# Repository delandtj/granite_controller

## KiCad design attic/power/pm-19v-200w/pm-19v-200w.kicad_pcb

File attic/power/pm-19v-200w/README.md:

# PM-19V-200W - OBSOLETE

Superseded by PM-19V-250W (power/pm-19v-250w/) on 2026-10-27.
Not for order, no further work. Kept for reference only.

Differences that make it obsolete: DOSA pin mount with a 1x5 1.27 mm
aux header (J2: OV_KILL, PGOOD, ID, TEMP, GND) instead of the screwed
mount and 2x3 aux block of docs/pm-interface.md, and 200 W instead of
250 W. Its silk was never tidied. Any future lower-power module will be
a new design, not a revision of this one.

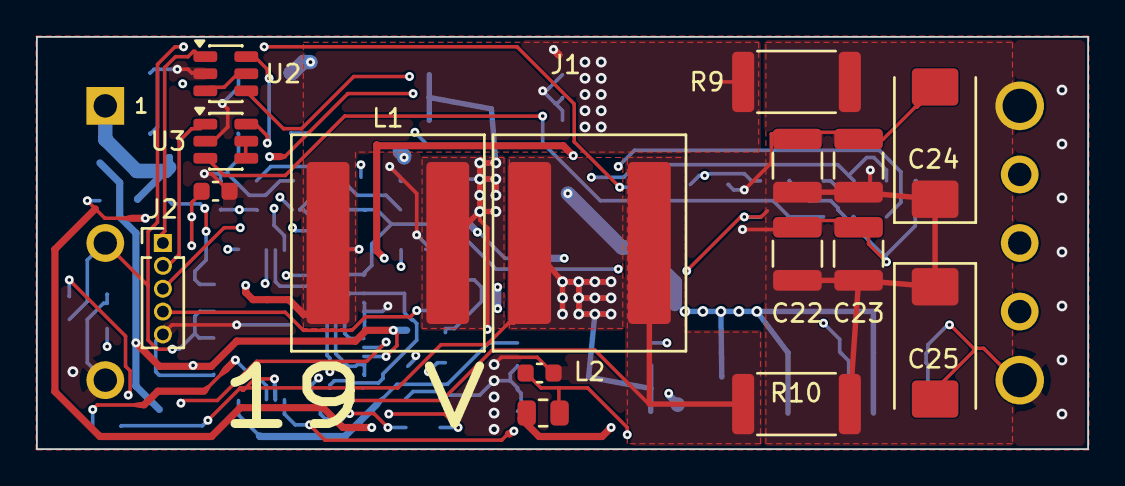
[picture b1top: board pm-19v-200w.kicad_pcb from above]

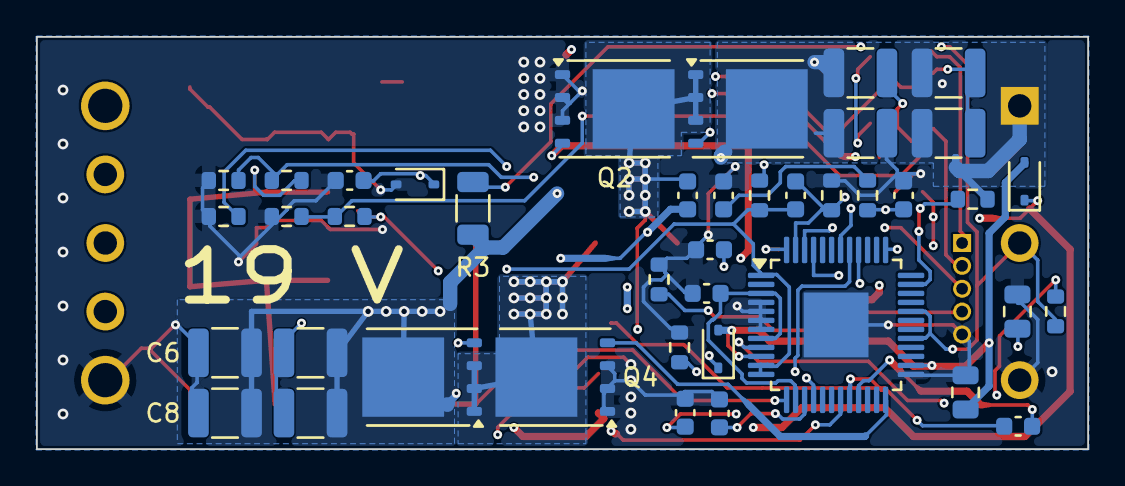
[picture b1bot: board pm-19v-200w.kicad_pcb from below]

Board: 4 copper layers, 58.4 x 22.9 mm, 58 parts (41 on the bottom side), 33 nets.

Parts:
C1, C2, C3, C4, C5, C6, C7, C8: 2.2u; C_1210_3225Metric
C9: 1u 100V; C_0805_2012Metric
C10, C15, C18, C19, C27, C28: 0.1u; C_0603_1608Metric
C11: 4.7u 25V; C_0805_2012Metric
C12: 47p; C_0603_1608Metric
C13: 2.2n; C_0603_1608Metric
C14: 100p; C_0603_1608Metric
C16, C17: 1n; C_0603_1608Metric
C20, C21, C22, C23: 22u; C_1210_3225Metric
C24, C25: 100u; CP_EIA-7343-31_Kemet-D
C26: 1u; C_0603_1608Metric
D1, D2: BAS21; D_SOD-323
D3: 4.7V; D_SOD-323
J1: Brick 1/8 (DOSA); Brick_Eighth_DOSA
J2: Aux; PinHeader_1x05_P1.27mm_Vertical
L1, L2: 22u Isat>=12A; L_Coilcraft_XAL1010-XXX
Q1, Q2, Q3, Q4: BSC070N10NS5; TDSON-8-1
R1: 10R; R_0603_1608Metric
R3: 976k 1206; R_1206_3216Metric
R4: 12.4k; R_0603_1608Metric
R5: 19.6k; R_0603_1608Metric
R6: 180k; R_0603_1608Metric
R7, R13, R15: 10k; R_0603_1608Metric
R8: 15k; R_0603_1608Metric
R9, R10: 8m 2512; R_2512_6332Metric
R11: 47k 0805; R_0805_2012Metric
R12: 178k; R_0603_1608Metric
R14: 133k; R_0603_1608Metric
R16: 10k (ID); R_0603_1608Metric
TH1: 10k NTC; R_0603_1608Metric
U1: LTC7810; LQFP-48-1EP_7x7mm_P0.5mm_EP3.6x3.6mm
U2, U3: MCP65R46-1.21; SOT-23-6

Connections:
/BG1: Q2.4, U1.37
/BG2: Q4.4, U1.24
/BOOST1: C18.1, D1.1, U1.40
/BOOST2: C19.1, D2.1, U1.21
/DRVCC: C11.1, D1.2, D2.2, U1.10, U1.26
/ID: J2.3, R16.1
/INTVCC: C10.1, U1.3, U1.8, U1.14
/OVLO: R4.2, R5.1, U1.9
/OV_KILL: J2.1, U2.1
/OV_REF: U2.3, U2.5
/PGOOD: J2.2, U3.1
/PG_REF: U3.4, U3.5
/RUN: J1.2, R3.2, R4.1, U1.29, U1.32
/SNS1P: L1.2, R9.1, U1.48
/SNS2P: L2.2, R10.1, U1.13
/SW1: C18.2, L1.1, Q1.1, Q1.2, Q1.3, Q2.5, U1.41
/SW2: C19.2, L2.1, Q3.1, Q3.2, Q3.3, Q4.5, U1.20
/TEMP: J2.4, TH1.1
/TG1: Q1.4, U1.42
/TG2: Q3.4, U1.19
/VAUX: C26.1, C27.1, C28.1, D3.1, R11.2, U2.6, U3.6
/VIN: C1.1, C2.1, C3.1, C4.1, C5.1, C6.1, C7.1, C8.1, J1.1, Q1.5, Q3.5, R1.1, R3.1, R11.1
/VIN_IC: C9.1, R1.2, U1.35
/VOUT: C12.1, C20.1, C21.1, C22.1, C23.1, C24.1, C25.1, J1.8, R6.1, R9.2, R10.2, R12.1, R14.1, U1.1, U1.11, U1.12
GND: C1.2, C2.2, C3.2, C4.2, C5.2, C6.2, C7.2, C8.2, C9.2, C10.2, C11.2, C13.2, C14.2, C15.2, C16.2, C17.2, C20.2, C21.2, C22.2, C23.2, C24.2, C25.2, C26.2, C27.2, C28.2, D3.2, J1.3, J1.4, J2.5, Q2.1, Q2.2, Q2.3, Q4.1, Q4.2, Q4.3, R5.2, R7.2, R13.2, R15.2, R16.2, TH1.2, U1.4, U1.5, U1.6, U1.7, U1.25, U1.49, U2.2, U3.2
unnamed: C13.1, R8.2
unnamed: C14.1, R8.1, U1.46
unnamed: C16.1, U1.15
unnamed: C15.1, U1.45
unnamed: C17.1, U1.16
unnamed: C12.2, R6.2, R7.1, U1.47
unnamed: R12.2, R13.1, U2.4
unnamed: R14.2, R15.1, U3.3

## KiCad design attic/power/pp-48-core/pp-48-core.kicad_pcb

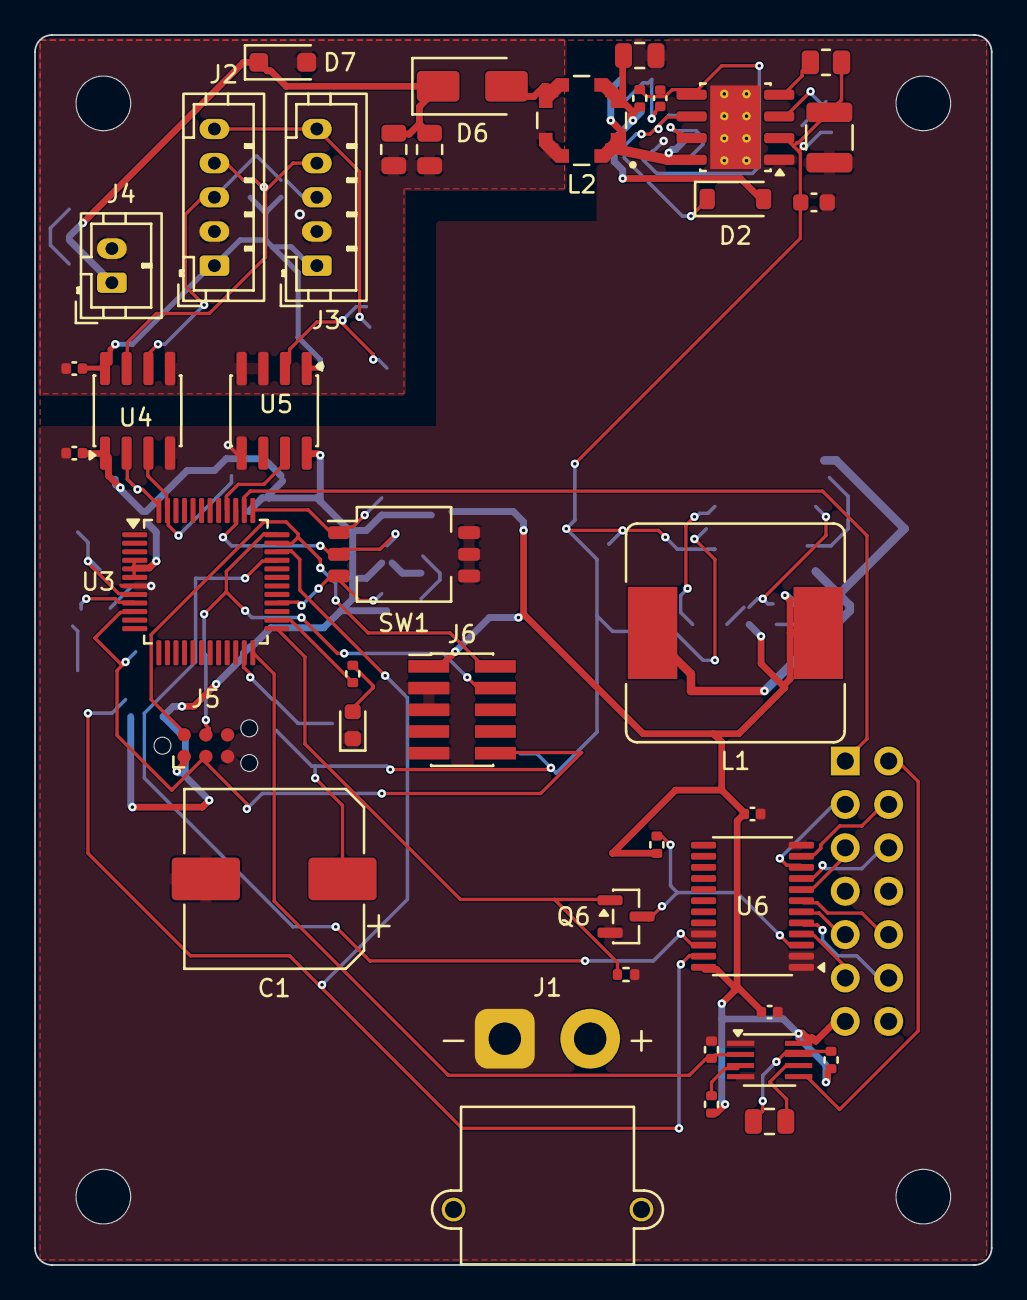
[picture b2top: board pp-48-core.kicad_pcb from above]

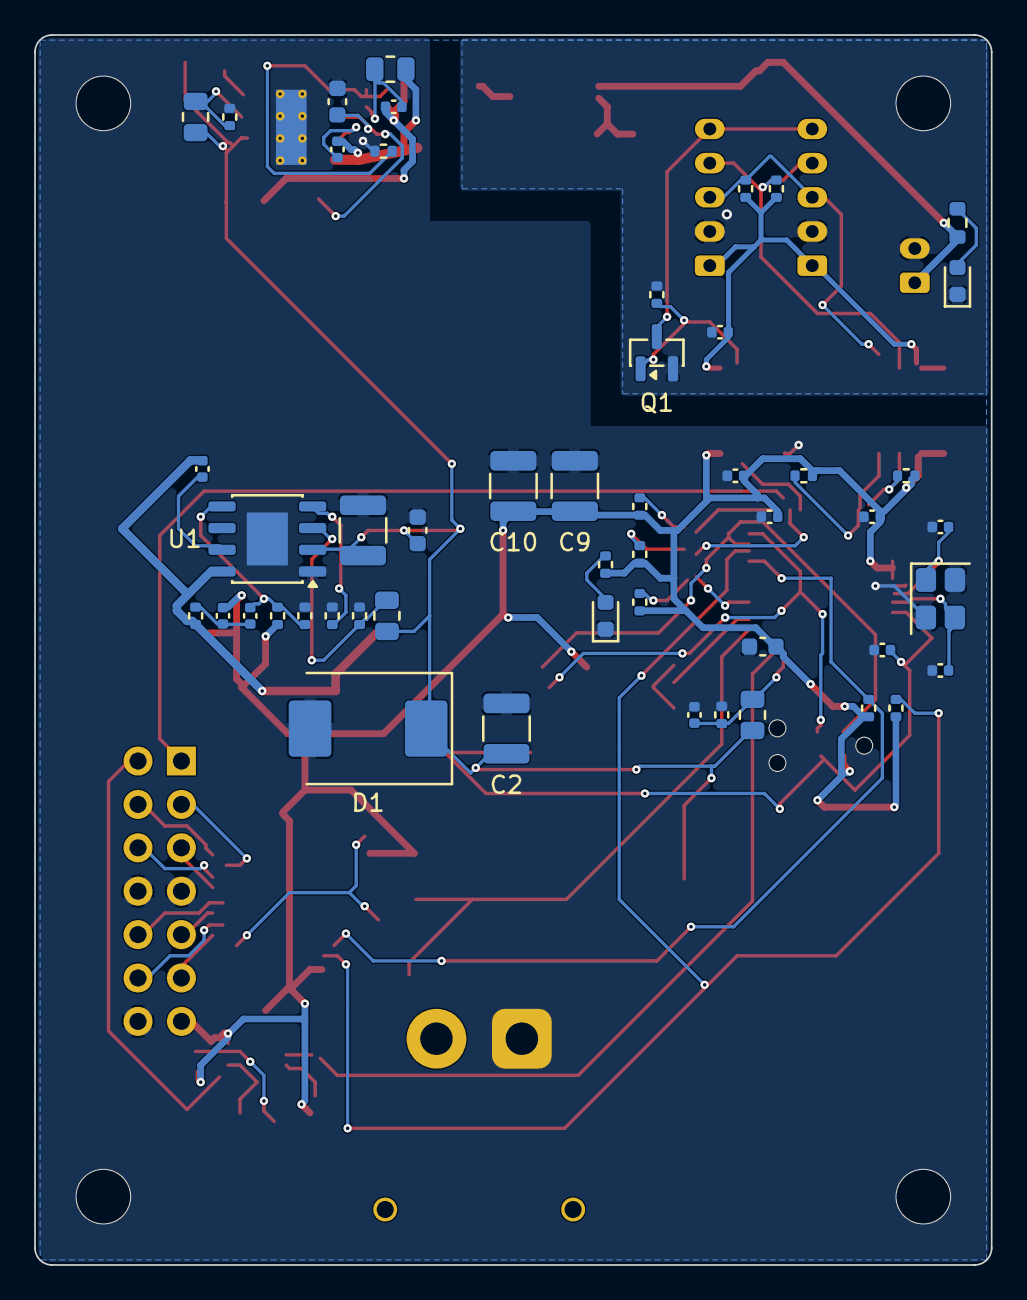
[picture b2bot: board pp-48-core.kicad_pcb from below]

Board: 4 copper layers, 56.0 x 72.0 mm, 95 parts (51 on the bottom side), 59 nets.

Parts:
C1: 47u 100V; CP_Elec_10x10
C2, C7, C11: 2.2u 100V; C_1210_3225Metric
C4: 2.2n 50V; C_0402_1005Metric
C5: 1.5n; C_0402_1005Metric
C6, C15, C17, C18, C20, C21, C24, C25, C26, C27, C28, C302: 100n; C_0402_1005Metric
C8, C12: 100n 100V; C_0603_1608Metric
C9, C10: 22u 10V; C_1210_3225Metric
C13: 10n 50V; C_0402_1005Metric
C14: 1n; C_0402_1005Metric
C16: 1u 25V; C_0603_1608Metric
C19: 4.7u; C_0603_1608Metric
C22, C23: 33p; C_0402_1005Metric
C29: 4.7u 25V; C_0805_2012Metric
C30, C31: 10u 25V; C_0805_2012Metric
C301: 10u; C_0805_2012Metric
D1: SMDJ60A; D_SMC
D2: 1N4148W; D_SOD-123
D3: GREEN 3V3; LED_0603_1608Metric
D4: GREEN RUN; LED_0603_1608Metric
D5: GREEN 12V; LED_0603_1608Metric
D6: SS110; D_SMA
D7: SMF13A; D_SOD-123F
H1, H2, H3, H4: MountingHole_3.2mm_M3
J1: XT30PW-M; AMASS_XT30PW-M_1x02_P2.50mm_Horizontal
J2: CTRL IN; JST_PH_B5B-PH-K_1x05_P2.00mm_Vertical
J3: CTRL OUT; JST_PH_B5B-PH-K_1x05_P2.00mm_Vertical
J4: 12V AUX OUT; JST_PH_B2B-PH-K_1x02_P2.00mm_Vertical
J5: SWD; Tag-Connect_TC2030-IDC-NL_2x03_P1.27mm_Vertical
J6: SWD; PinHeader_2x05_P1.27mm_Vertical_SMD
J301: CHAIN OUT; PinSocket_2x07_P2.54mm_Horizontal
L1: 33u; L_Bourns_SRR1260
L2: 33u; L_Coilcraft_LPD5030V
Q1, Q6: 2N7002; SOT-23
R3: 1M; R_0805_2012Metric
R4: 52.3k; R_0402_1005Metric
R5: 41.2k; R_0402_1005Metric
R6: 86.6k; R_0402_1005Metric
R7: 49.9k; R_0402_1005Metric
R8: 453k; R_0402_1005Metric
R9: 4.7k; R_0603_1608Metric
R10: 100k; R_0805_2012Metric
R11: 4.22k; R_0402_1005Metric
R12: 169k; R_0805_2012Metric
R13: 200k; R_0805_2012Metric
R14: 18.7k; R_0402_1005Metric
R15: 220k; R_0805_2012Metric
R16, R31, R303: 10k; R_0402_1005Metric
R17: 2k; R_0402_1005Metric
R18, R19: 1k; R_0402_1005Metric
R20, R21, R22, R30, R32, R301, R302: 100k; R_0402_1005Metric
R23, R24: 2.2k; R_0402_1005Metric
R26, R27, R28, R29: 4.7k; R_0402_1005Metric
SW1: ADR; SW_DIP_SPSTx03_Slide_KingTek_DSHP03TS_W7.62mm_P1.27mm
U1: LM5164DDA; HSOP-8-1EP_3.9x4.9mm_P1.27mm_EP2.41x3.1mm
U2: LM5018MRX/NOPB; SOIC-8-1EP_3.9x4.9mm_P1.27mm_EP2.95x4.9mm_Mask2.71x3.4mm_Th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
U3: STM32G070CBT6; LQFP-48_7x7mm_P0.5mm
U4: ISO1640BD; SOIC-8_3.9x4.9mm_P1.27mm
U5: ISO7721D; SOIC-8_3.9x4.9mm_P1.27mm
U6: TCA9548APWR; TSSOP-24_4.4x7.8mm_P0.65mm
U301: 74LVC1G123; SSOP-8_2.95x2.8mm_P0.65mm
Y1: 8MHz; Crystal_SMD_3225-4Pin_3.2x2.5mm

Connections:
+3V3: C5.2, C9.1, C10.1, C18.1, C19.1, C20.1, C25.1, C27.1, C28.1, C302.1, J5.1, J6.1, J301.13, L1.2, R6.1, R18.1, R20.1, R21.1, R22.1, R23.1, R24.1, R26.1, R27.1, R31.1, R301.1, R303.1, U3.4, U3.5, U3.6, U4.1, U5.8, U6.24, U301.8
/Chain/CEXT: C301.2, U301.6
/Chain/PRESS_CLRN: R303.2, U301.3
/Chain/PRESS_EN: J301.2, U301.5
/Chain/RCEXT: C301.1, R301.2, U301.7
/EXP_RSTN: J301.1, U3.38
/INT_OUT: U3.40, U5.7
/Link/CTRL_INT: J2.5, J3.5, Q1.3
/Link/CTRL_SCL: J2.3, J3.3, R29.2, U4.6
/Link/CTRL_SDA: J2.4, J3.4, R28.2, U4.7
/Link/ISO_OUTA: Q1.1, R30.1, U5.2
/MCU/ADR0: R20.2, SW1.1, U3.37
/MCU/ADR1: R21.2, SW1.2, U3.39
/MCU/ADR2: R22.2, SW1.3, U3.28
/MCU/LEDRUN_A: D4.2, R19.2
/MCU/LED_RUN: R19.1, U3.26
/MCU/NRST: C21.1, J5.3, J6.10, U3.10
/MCU/OSC_IN: C22.1, U3.8, Y1.1
/MCU/OSC_OUT: C23.1, U3.9, Y1.3
/MCU/SWCLK: J5.4, J6.4, U3.36
/MCU/SWDIO: J5.2, J6.2, U3.35
/MUX_RST: Q6.1, R32.1, U3.25
/Mux/MUX_RSTN: Q6.3, R31.2, U6.3
/PRESS_TRIG: R302.1, U3.24, U301.2
/SCL1: R27.2, U3.47, U4.3
/SCL2: R24.2, U3.33, U6.22
/SDA1: R26.2, U3.48, U4.2
/SDA2: R23.2, U3.34, U6.23
/Supplies/BST1: C4.1, U1.7
/Supplies/BST2: C13.1, U2.7
/Supplies/EN1: R3.2, R4.1, U1.3
/Supplies/FB1: C6.2, R6.2, R7.1, U1.5
/Supplies/FB2: C15.2, R14.2, R17.1, U2.5
/Supplies/INJ1: C5.1, C6.1, R8.2
/Supplies/INJ2: C14.1, C15.1, R13.2
/Supplies/LED12_A: D5.2, R9.2
/Supplies/LED33_A: D3.2, R18.2
/Supplies/RON1: R5.1, U1.4
/Supplies/RON2: R12.2, U2.4
/Supplies/SEC2: D6.2, L2.3
/Supplies/SW1: C4.2, L1.1, R8.1, U1.8
/Supplies/SW2: C13.2, L2.1, R13.1, U2.8
/Supplies/UVLO2: R10.2, R11.1, U2.3
/Supplies/VCC2: C16.1, D2.1, U2.6
/Supplies/VOUT1: C14.2, C29.1, D2.2, L2.2, R14.1
/UNIT1_SCL: J301.12, U6.5
/UNIT1_SDA: J301.11, U6.4
/UNIT2_SCL: J301.10, U6.7
/UNIT2_SDA: J301.9, U6.6
/UNIT3_SCL: J301.6, U6.9
/UNIT3_SDA: J301.5, U6.8
/UNIT4_SCL: J301.4, U6.11
/UNIT4_SDA: J301.3, U6.10
/VIN_SNS: C17.1, R15.2, R16.1, U3.23
CTRL_3V3: C24.1, C26.1, J2.1, J3.1, R28.1, R29.1, U4.8, U5.1
CTRL_12V: C30.1, C31.1, D6.1, D7.1, J4.1, R9.1
CTRL_GND: C24.2, C26.2, C30.2, C31.2, D5.1, D7.2, J2.2, J3.2, J4.2, L2.4, Q1.2, R30.2, U4.5, U5.3, U5.4
GND: C1.2, C2.2, C7.2, C8.2, C9.2, C10.2, C11.2, C12.2, C16.2, C17.2, C18.2, C19.2, C20.2, C21.2, C22.2, C23.2, C25.2, C27.2, C28.2, C29.2, C302.2, D1.2, D3.1, D4.1, J1.1, J5.5, J6.3, J6.5, J6.9, J301.7, J301.8, J301.14, Q6.2, R4.2, R5.2, R7.2, R11.2, R16.2, R17.2, R32.2, R302.2, SW1.4, SW1.5, SW1.6, U1.1, U1.9, U2.1, U2.9, U3.7, U4.4, U5.5, U6.1, U6.2, U6.12, U6.21, U301.1, U301.4, Y1.2, Y1.4
VIN: C1.1, C2.1, C7.1, C8.1, C11.1, C12.1, D1.1, J1.2, R3.1, R10.1, R12.1, R15.1, U1.2, U2.2

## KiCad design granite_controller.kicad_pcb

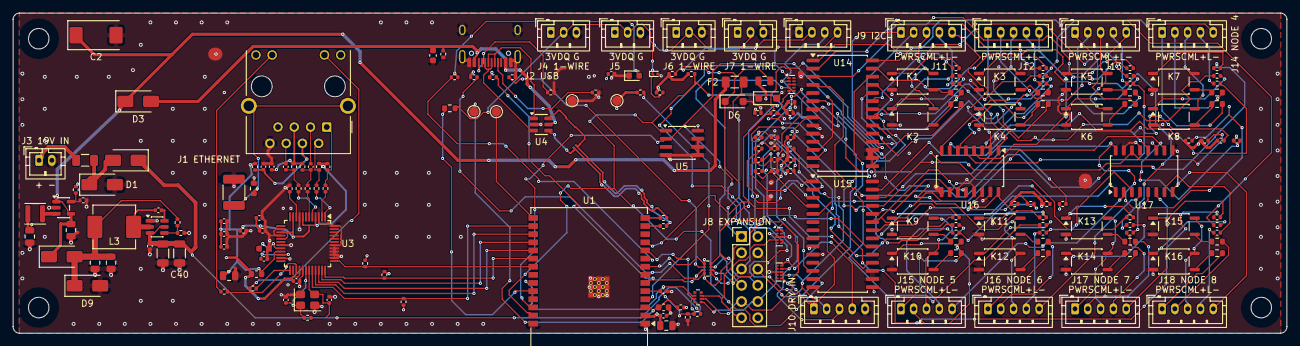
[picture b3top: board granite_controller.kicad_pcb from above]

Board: 4 copper layers, 199.0 x 50.0 mm, 207 parts (0 on the bottom side), 187 nets.

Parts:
C2: 220u/10V Ta-poly; CP_EIA-7343-31_Kemet-D
C3, C4, C44, C45: 22u; C_0805_2012Metric
C5, C6, C7, C8, C9, C10, C11, C13, C15, C38, C46, C47, C48, C49, C50, C51: 100n; C_0402_1005Metric
C12, C32: 10u; C_0805_2012Metric
C14: 1u; C_0603_1608Metric
C26, C27: 15p; C_0402_1005Metric
C28, C29: 6.8n; C_0402_1005Metric
C30: 4.7u; C_0603_1608Metric
C31, C35: 10n; C_0402_1005Metric
C34: 22n; C_0402_1005Metric
C36: 1n/2kV; C_1812_4532Metric
C40, C41: 4.7u/50V; C_1206_3216Metric
C42, C43: 100n/50V; C_0402_1005Metric
C52: 2.2u/25V; C_0603_1608Metric
D1: SMAJ22A; D_SMA
D2, D3, D8: SS34; D_SMA
D4: green; LED_0603_1608Metric
D5: ESD9L5.0ST5G; D_SOD-923
D6: SMF3.3A; D_SOD-123F
D7: SMF5.0A; D_SOD-123F
D9: SMAJ6.0A; D_SMA
F1: PTC 350mA; Fuse_0805_2012Metric
F2: PTC 500mA; Fuse_1206_3216Metric
F3: PTC 0.75A; Fuse_1206_3216Metric
H1, H2, H3, H4: MountingHole_3.2mm_M3
J1: HR911105A; RJ45_Hanrun_HR911105A_Horizontal
J2: TYPE-C-31-M-12; USB_C_Receptacle_HRO_TYPE-C-31-M-12
J3: 19V_IN; JST_PH_B2B-PH-K_1x02_P2.00mm_Vertical
J4, J5, J6, J7: 1WIRE; JST_PH_B3B-PH-K_1x03_P2.00mm_Vertical
J8: EXPANSION; PinHeader_2x06_P2.54mm_Vertical
J9: I2C_SENSOR; JST_PH_B4B-PH-K_1x04_P2.00mm_Vertical
J10: DRY_IN; JST_PH_B5B-PH-K_1x05_P2.00mm_Vertical
J11: MB01_FP; JST_PH_B5B-PH-K_1x05_P2.00mm_Vertical
J12: MB02_FP; JST_PH_B5B-PH-K_1x05_P2.00mm_Vertical
J13: MB03_FP; JST_PH_B5B-PH-K_1x05_P2.00mm_Vertical
J14: MB04_FP; JST_PH_B5B-PH-K_1x05_P2.00mm_Vertical
J15: MB05_FP; JST_PH_B5B-PH-K_1x05_P2.00mm_Vertical
J16: MB06_FP; JST_PH_B5B-PH-K_1x05_P2.00mm_Vertical
J17: MB07_FP; JST_PH_B5B-PH-K_1x05_P2.00mm_Vertical
J18: MB08_FP; JST_PH_B5B-PH-K_1x05_P2.00mm_Vertical
K1, K2, K3, K4, K5, K6, K7, K8, K9, K10, K11, K12, K13, K14, K15, K16: TLP176AM; SOIC-4_4.55x3.7mm_P2.54mm
L1: 2u2 SWPA3015S2R2MT; L_Sunlord_SWPA3015S
L2: 120R@100MHz; L_0603_1608Metric
L3: 3u3; L_Changjiang_FXL0630
R1, R37, R63: 100k; R_0402_1005Metric
R2: 22.1k; R_0402_1005Metric
R3, R4: 330; R_0402_1005Metric
R5, R6, R13, R14, R30, R65: 4.7k; R_0402_1005Metric
R7, R16, R17, R18, R19, R27, R32, R33, R59, R60, R61, R62, R64: 10k; R_0402_1005Metric
R8, R55, R56, R57, R58: 1k; R_0402_1005Metric
R9, R10, R11, R12: 33; R_0402_1005Metric
R15, R38: 12.4k 1%; R_0402_1005Metric
R20, R21, R22, R23: 49.9; R_0402_1005Metric
R24, R25: 5.1k; R_0402_1005Metric
R26: 10; R_0402_1005Metric
R28: 1M; R_0603_1608Metric
R29: 1M; R_0402_1005Metric
R34, R35: 22; R_0402_1005Metric
R36, R201, R202, R203, R204, R205, R206, R207, R208, R209, R210, R211, R212, R213, R214, R215, R216: 100; R_0603_1608Metric
R39, R40, R41, R42, R43, R44, R45, R46: 47k; R_0402_1005Metric
R47, R48, R49, R50, R51, R52, R53, R54: 220; R_0402_1005Metric
R101, R102, R103, R104, R105, R106, R107, R108, R109, R110, R111, R112, R113, R114, R115, R116: 270; R_0402_1005Metric
RN1, RN2: 4x330; R_Array_Convex_4x0402
TP1: EN; TestPoint_Pad_D1.5mm
TP2: BOOT; TestPoint_Pad_D1.5mm
TP3: GND; TestPoint_Pad_D1.5mm
TP4: 3V3; TestPoint_Pad_D1.5mm
U1: ESP32-C6-WROOM-1-N8; ESP32-C6-WROOM-1
U2: TLV62569DBV; SOT-23-5
U3: W5500; LQFP-48_7x7mm_P0.5mm
U4: USBLC6-2SC6; SOT-23-6
U5: TMP1075D; SOIC-8_3.9x4.9mm_P1.27mm
U6, U7, U18: TPD4E05U06DQA; USON-10_2.5x1.0mm_P0.5mm
U8: LMR51430YDDCR; SOT-23-6
U14, U15: MCP23017-E/SO; SOIC-28W_7.5x17.9mm_P1.27mm
U16, U17: TLP290-4; SOP-16_4.55x10.3mm_P1.27mm
Y2: 25MHz 12pF YXC; Crystal_SMD_Abracon_ABM8G-4Pin_3.2x2.5mm

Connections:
+3V3: C4.1, C11.1, C12.1, C13.1, C15.1, C38.1, C46.1, F1.1, J1.9, J1.12, J4.1, J5.1, J6.1, J7.1, L1.1, L2.1, R1.2, R5.1, R6.1, R7.1, R13.1, R14.1, R16.1, R17.1, R18.1, R27.1, R30.1, R33.1, R39.1, R40.1, R41.1, R42.1, R43.1, R44.1, R45.1, R46.1, R59.1, R60.1, R61.1, R62.1, TP4.1, U1.2, U3.28, U5.8, U14.9, U15.9, U15.15
+5V: C2.1, C3.1, D2.1, D3.1, F2.1, U2.1, U2.4
/Ethernet/+3V3A: C5.1, C6.1, C7.1, C8.1, C9.1, C10.1, C32.1, L2.2, R20.2, R21.2, R26.2, U3.4, U3.8, U3.11, U3.15, U3.17, U3.21
/Ethernet/ETH_1V2O: C31.1, U3.22
/Ethernet/ETH_EXRES: R15.1, U3.10
/Ethernet/ETH_LEDK_ACT: J1.11, R4.1
/Ethernet/ETH_LEDK_LINK: J1.10, R3.1
/Ethernet/ETH_LED_ACT: R4.2, U3.27
/Ethernet/ETH_LED_LINK: R3.2, U3.25
/Ethernet/ETH_RCT: C35.1, J1.5, R22.2, R23.2
/Ethernet/ETH_RX+: C28.2, J1.3
/Ethernet/ETH_RX-: C29.2, J1.6
/Ethernet/ETH_RXN: R12.1, U3.5
/Ethernet/ETH_RXN_T: C29.1, R12.2, R23.1
/Ethernet/ETH_RXP: R11.1, U3.6
/Ethernet/ETH_RXP_T: C28.1, R11.2, R22.1
/Ethernet/ETH_SHLD: C36.1, J1.SH, R28.1
/Ethernet/ETH_TCT: C34.1, J1.4, R26.1
/Ethernet/ETH_TOCAP: C30.1, U3.20
/Ethernet/ETH_TX+: J1.1, R9.2, R20.1
/Ethernet/ETH_TX-: J1.2, R10.2, R21.1
/Ethernet/ETH_TXN: R10.1, U3.1
/Ethernet/ETH_TXP: R9.1, U3.2
/Ethernet/ETH_XI: C26.1, R29.1, U3.30, Y2.1
/Ethernet/ETH_XO: C27.1, R29.2, U3.31, Y2.3
/Expansion header/DRYC1: J10.1, R55.2, R59.2, U18.1
/Expansion header/DRYC2: J10.2, R56.2, R60.2, U18.2
/Expansion header/DRYC3: J10.3, R57.2, R61.2, U18.4
/Expansion header/DRYC4: J10.4, R58.2, R62.2, U18.5
/Expansion header/HDR_3V3: D6.1, F1.2, J8.1, J9.2
/Expansion header/HDR_5V: D7.1, F2.2, J8.2
/Expansion header/HDR_INT: J8.8, RN1.4, U6.5
/Expansion header/HDR_IO5: J8.9, RN2.1, U7.1
/Expansion header/HDR_IO8: J8.10, RN2.2, U7.2
/Expansion header/HDR_IO15: J8.11, RN2.3, U7.4
/Expansion header/HDR_SCL: J8.5, J9.4, RN1.1, U6.1
/Expansion header/HDR_SDA: J8.6, J9.3, RN1.2, U6.2
/Expansion header/HDR_nRESET: J8.7, RN1.3, U6.4
/MCU/C6_BOOT: TP2.1, U1.15
/MCU/C6_EN: C14.1, R7.2, TP1.1, U1.3
/MCU/C6_USB_D+: R34.2, U1.14
/MCU/C6_USB_D-: R35.2, U1.13
/MCU/LED_A: D4.2, R8.2
/MCU/LED_HB: R8.1, U1.9
/MCU/OW_DATA: D5.1, J4.2, J5.2, J6.2, J7.2, R30.2, R36.2
/MCU/OW_MCU: R36.1, U1.24, U1.25
/MCU/USB_CC1: J2.A5, R25.1
/MCU/USB_CC2: J2.B5, R24.1
/MCU/USB_CONN_D+: J2.A6, J2.B6, U4.3
/MCU/USB_CONN_D-: J2.A7, J2.B7, U4.1
/MCU/USB_D+: R34.1, U4.4
/MCU/USB_D-: R35.1, U4.6
/Power/BUCK_5V: C44.1, C45.1, D2.2, D9.1, L3.2, R37.1
/Power/FB_3V3: R1.1, R2.1, U2.5
/Power/FB_5V: R37.2, R38.1, U8.4
/Power/SW_3V3: L1.2, U2.3
/Power/SW_5V: C43.2, L3.1, U8.2
/Power/VIN_19V: C40.1, C41.1, C42.1, D8.1, R63.1, U8.3, U8.5
/Power/VIN_RAW: F3.1, J3.1
/Relay channels/MB1_COM: J11.3, K1.6, K2.6
/Relay channels/MB1_PLED_N: J11.5, U16.2
/Relay channels/MB1_PLED_P: J11.4, R47.1
/Relay channels/MB1_PWR_B: J11.1, R202.2
/Relay channels/MB1_RST_B: J11.2, R201.2
/Relay channels/MB2_COM: J12.3, K3.6, K4.6
/Relay channels/MB2_PLED_N: J12.5, U16.4
/Relay channels/MB2_PLED_P: J12.4, R48.1
/Relay channels/MB2_PWR_B: J12.1, R204.2
/Relay channels/MB2_RST_B: J12.2, R203.2
/Relay channels/MB3_COM: J13.3, K5.6, K6.6
/Relay channels/MB3_PLED_N: J13.5, U16.6
/Relay channels/MB3_PLED_P: J13.4, R49.1
/Relay channels/MB3_PWR_B: J13.1, R206.2
/Relay channels/MB3_RST_B: J13.2, R205.2
/Relay channels/MB4_COM: J14.3, K7.6, K8.6
/Relay channels/MB4_PLED_N: J14.5, U16.8
/Relay channels/MB4_PLED_P: J14.4, R50.1
/Relay channels/MB4_PWR_B: J14.1, R208.2
/Relay channels/MB4_RST_B: J14.2, R207.2
/Relay channels/MB5_COM: J15.3, K9.6, K10.6
/Relay channels/MB5_PLED_N: J15.5, U17.2
/Relay channels/MB5_PLED_P: J15.4, R51.1
/Relay channels/MB5_PWR_B: J15.1, R210.2
/Relay channels/MB5_RST_B: J15.2, R209.2
/Relay channels/MB6_COM: J16.3, K11.6, K12.6
/Relay channels/MB6_PLED_N: J16.5, U17.4
/Relay channels/MB6_PLED_P: J16.4, R52.1
/Relay channels/MB6_PWR_B: J16.1, R212.2
/Relay channels/MB6_RST_B: J16.2, R211.2
/Relay channels/MB7_COM: J17.3, K13.6, K14.6
/Relay channels/MB7_PLED_N: J17.5, U17.6
/Relay channels/MB7_PLED_P: J17.4, R53.1
/Relay channels/MB7_PWR_B: J17.1, R214.2
/Relay channels/MB7_RST_B: J17.2, R213.2
/Relay channels/MB8_COM: J18.3, K15.6, K16.6
/Relay channels/MB8_PLED_N: J18.5, U17.8
/Relay channels/MB8_PLED_P: J18.4, R54.1
/Relay channels/MB8_PWR_B: J18.1, R216.2
/Relay channels/MB8_RST_B: J18.2, R215.2
/Relay channels/NODE_ON1: R39.2, U15.21, U16.16
/Relay channels/NODE_ON2: R40.2, U15.22, U16.14
/Relay channels/NODE_ON3: R41.2, U15.23, U16.12
/Relay channels/NODE_ON4: R42.2, U15.24, U16.10
/Relay channels/NODE_ON5: R43.2, U15.25, U17.16
/Relay channels/NODE_ON6: R44.2, U15.26, U17.14
/Relay channels/NODE_ON7: R45.2, U15.27, U17.12
/Relay channels/NODE_ON8: R46.2, U15.5, U17.10
/Relay channels/PWR_DRV1: R102.1, U14.21
/Relay channels/PWR_DRV2: R104.1, U14.22
/Relay channels/PWR_DRV3: R106.1, U14.23
/Relay channels/PWR_DRV4: R108.1, U14.24
/Relay channels/PWR_DRV5: R110.1, U14.25
/Relay channels/PWR_DRV6: R112.1, U14.26
/Relay channels/PWR_DRV7: R114.1, U14.27
/Relay channels/PWR_DRV8: R116.1, U14.28
/Relay channels/RST_DRV1: R101.1, U14.1
/Relay channels/RST_DRV2: R103.1, U14.2
/Relay channels/RST_DRV3: R105.1, U14.3
/Relay channels/RST_DRV4: R107.1, U14.4
/Relay channels/RST_DRV5: R109.1, U14.5
/Relay channels/RST_DRV6: R111.1, U14.6
/Relay channels/RST_DRV7: R113.1, U14.7
/Relay channels/RST_DRV8: R115.1, U14.8
DRY_IN1: C47.1, R55.1, U15.1
DRY_IN2: C48.1, R56.1, U15.2
DRY_IN3: C49.1, R57.1, U15.3
DRY_IN4: C50.1, R58.1, U15.4
ETH_CS: R16.2, U1.16, U3.32
ETH_INT: R17.2, U1.20, U3.36
ETH_MISO: U1.19, U3.34
ETH_MOSI: U1.18, U3.35
ETH_RST: R18.2, U1.21, U3.37
ETH_SCLK: U1.17, U3.33
EXP_INT: R33.2, RN1.5, U1.8, U14.20, U15.20
EXP_nRESET: R19.1, RN1.6, U1.4
EXP_nRESET_INT: R32.1, U1.11, U14.18, U15.18
GND: C2.2, C3.2, C4.2, C5.2, C6.2, C7.2, C8.2, C9.2, C10.2, C11.2, C12.2, C13.2, C14.2, C15.2, C26.2, C27.2, C30.2, C31.2, C32.2, C34.2, C35.2, C36.2, C38.2, C40.2, C41.2, C42.2, C44.2, C45.2, C46.2, C47.2, C48.2, C49.2, C50.2, C51.2, C52.2, D1.2, D4.1, D5.2, D6.2, D7.2, D9.2, J1.8, J2.A1, J2.A12, J2.B1, J2.B12, J2.SH, J3.2, J4.3, J5.3, J6.3, J7.3, J8.3, J8.4, J8.12, J9.1, J10.5, K1.3, K2.3, K3.3, K4.3, K5.3, K6.3, K7.3, K8.3, K9.3, K10.3, K11.3, K12.3, K13.3, K14.3, K15.3, K16.3, R2.2, R15.2, R19.2, R24.2, R25.2, R28.2, R32.2, R38.2, R64.2, R65.2, TP3.1, U1.1, U1.28, U1.29, U2.2, U3.3, U3.9, U3.14, U3.16, U3.19, U3.23, U3.29, U3.38, U3.39, U3.40, U3.41, U3.42, U3.48, U4.2, U5.4, U5.5, U5.6, U5.7, U6.3, U6.8, U7.3, U7.8, U8.1, U14.10, U14.15, U14.16, U14.17, U15.10, U15.16, U15.17, U16.9, U16.11, U16.13, U16.15, U17.9, U17.11, U17.13, U17.15, U18.3, U18.8, Y2.2, Y2.4
GPIO_IO8: R27.2, RN2.7, U1.10
GPIO_IO15: RN2.6, U1.23
I2C_EXT_SCL: R13.2, RN1.8, U1.7
I2C_EXT_SDA: R14.2, RN1.7, U1.6
I2C_INT_SCL: R5.2, U1.26, U5.2, U14.12, U15.12
I2C_INT_SDA: R6.2, U1.27, U5.1, U14.13, U15.13
unnamed: D1.1, D8.2, F3.2
unnamed: K1.1, R101.2
unnamed: K1.4, R201.1
unnamed: K2.1, R102.2
unnamed: K2.4, R202.1
unnamed: K3.1, R103.2
unnamed: K3.4, R203.1
unnamed: K4.1, R104.2
unnamed: K4.4, R204.1
unnamed: K5.1, R105.2
unnamed: K5.4, R205.1
unnamed: K6.1, R106.2
unnamed: K6.4, R206.1
unnamed: K7.1, R107.2
unnamed: K7.4, R207.1
unnamed: K8.1, R108.2
unnamed: K8.4, R208.1
unnamed: K9.1, R109.2
unnamed: K9.4, R209.1
unnamed: K10.1, R110.2
unnamed: K10.4, R210.1
unnamed: K11.1, R111.2
unnamed: K11.4, R211.1
unnamed: K12.1, R112.2
unnamed: K12.4, R212.1
unnamed: K13.1, R113.2
unnamed: K13.4, R213.1
unnamed: K14.1, R114.2
unnamed: K14.4, R214.1
unnamed: K15.1, R115.2
unnamed: K15.4, R215.1
unnamed: K16.1, R116.2
unnamed: K16.4, R216.1
unnamed: R47.2, U16.1
unnamed: R48.2, U16.3
unnamed: R49.2, U16.5
unnamed: R50.2, U16.7
unnamed: R51.2, U17.1
unnamed: R52.2, U17.3
unnamed: R53.2, U17.5
unnamed: R54.2, U17.7
unnamed: C43.1, U8.6
VBUS: C52.1, D3.2, J2.A4, J2.A9, J2.B4, J2.B9, R65.1, U4.5
VIN_SENSE: C51.1, R63.2, R64.1, U1.5

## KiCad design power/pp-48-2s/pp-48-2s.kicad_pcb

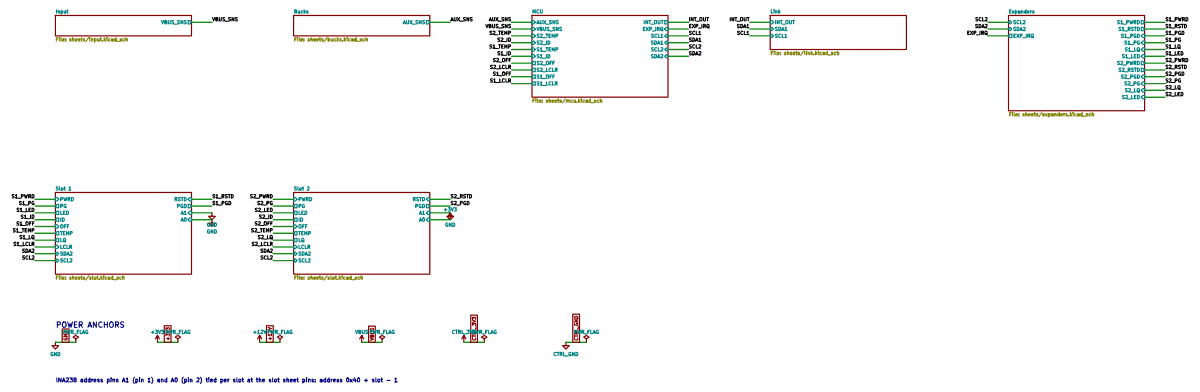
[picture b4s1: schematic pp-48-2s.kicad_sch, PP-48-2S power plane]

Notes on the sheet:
POWER ANCHORS
INA238 address pins A1 (pin 1) and A0 (pin 2) tied per slot at the slot sheet pins: address 0x40 + slot - 1

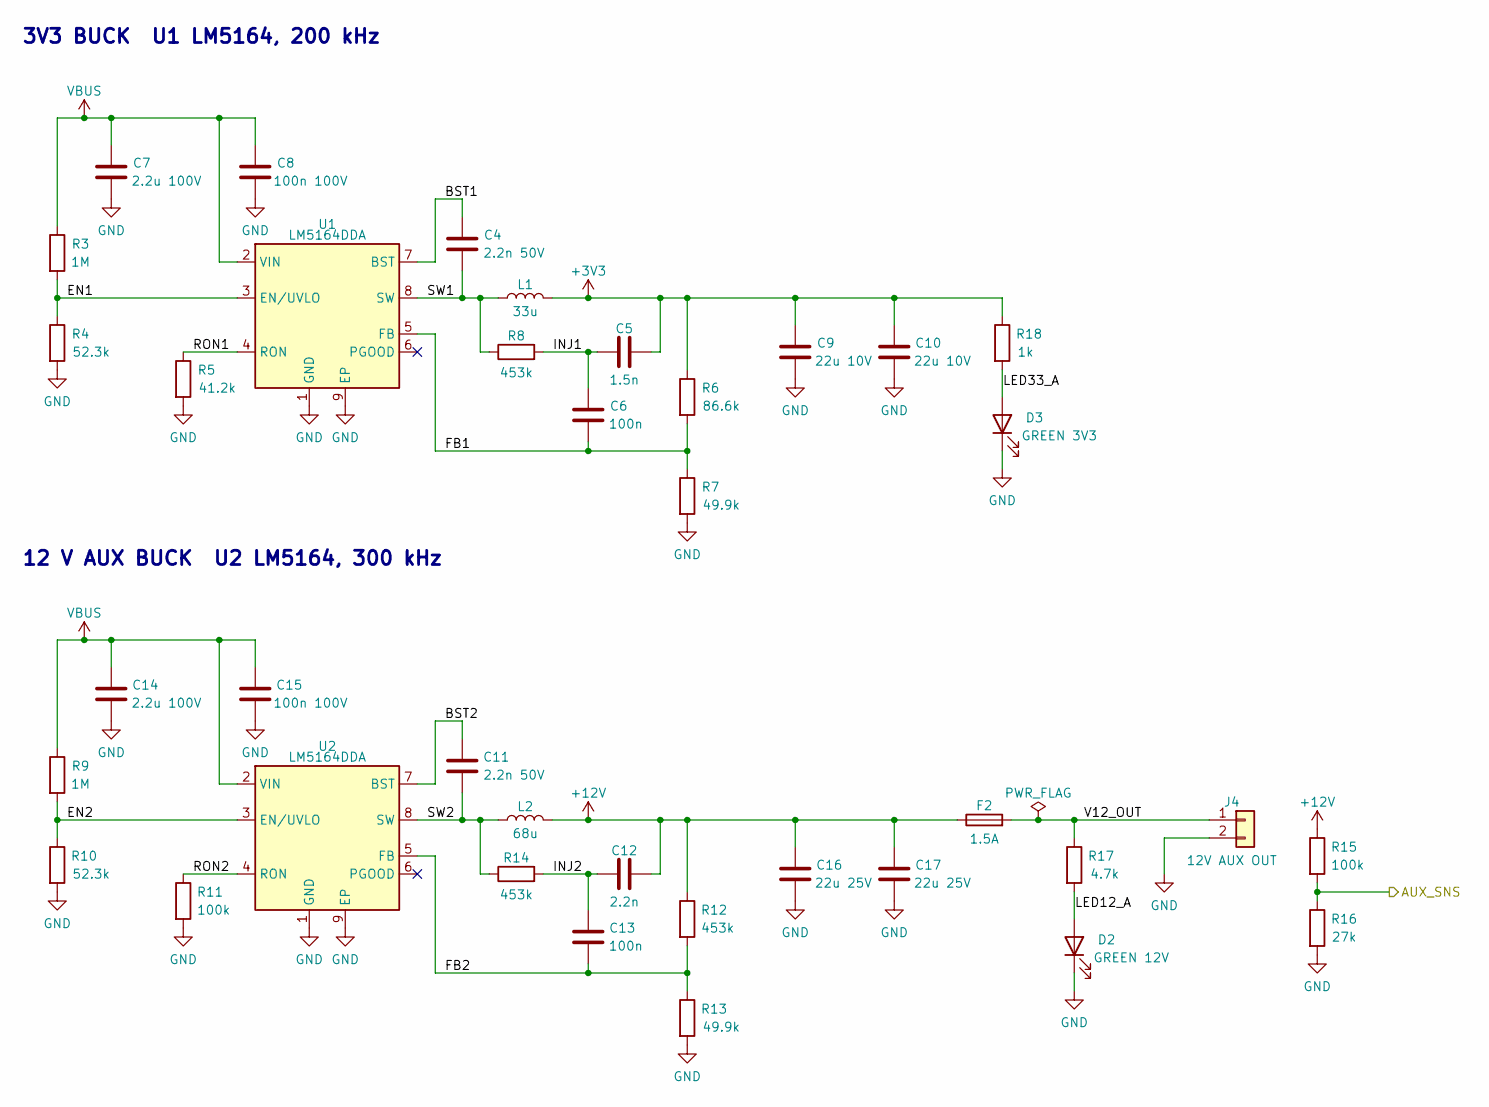
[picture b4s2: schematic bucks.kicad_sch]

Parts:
C4, C11: 2.2n 50V; C_0402_1005Metric
C5: 1.5n; C_0402_1005Metric
C6, C13: 100n; C_0402_1005Metric; LCSC C1525
C7, C14: 2.2u 100V; C_1210_3225Metric; LCSC C338133
C8, C15: 100n 100V; C_0603_1608Metric
C9, C10: 22u 10V; C_1210_3225Metric
C12: 2.2n; C_0402_1005Metric
C16, C17: 22u 25V; C_1210_3225Metric
D2: GREEN 12V; LED_0603_1608Metric; LCSC C2297
D3: GREEN 3V3; LED_0603_1608Metric; LCSC C2297
F2: 1.5A; Fuse_1206_3216Metric
J4: 12V AUX OUT; JST_PH_B2B-PH-K_1x02_P2.00mm_Vertical; LCSC C131337
L1: 33u; L_12x12mm_H6mm; MPN Bourns SRR1260-330M; LCSC C840528
L2: 68u; L_12x12mm_H6mm; MPN Bourns SRR1260-680M
R3, R9: 1M; R_0805_2012Metric
R4, R10: 52.3k; R_0402_1005Metric
R5: 41.2k; R_0402_1005Metric
R6: 86.6k; R_0402_1005Metric
R7, R13: 49.9k; R_0402_1005Metric
R8, R12, R14: 453k; R_0402_1005Metric
R11, R15: 100k; R_0402_1005Metric; LCSC C25741
R16: 27k; R_0402_1005Metric
R17: 4.7k; R_0603_1608Metric
R18: 1k; R_0402_1005Metric; LCSC C11702
U1, U2: LM5164DDA; HSOP-8-1EP_3.9x4.9mm_P1.27mm_EP2.41x3.1mm; LCSC C477928

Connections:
+3V3: C5.2, C9.1, C10.1, L1.2, R6.1, R18.1; also elsewhere on the board
+12V: C12.2, C16.1, C17.1, F2.1, L2.2, R12.1, R15.1
/AUX_SNS: R15.2, R16.1; also elsewhere on the board
/Bucks/BST1: C4.1, U1.7 (BST)
/Bucks/BST2: C11.1, U2.7 (BST)
/Bucks/EN1: R3.2, R4.1, U1.3 (EN/UVLO)
/Bucks/EN2: R9.2, R10.1, U2.3 (EN/UVLO)
/Bucks/FB1: C6.2, R6.2, R7.1, U1.5 (FB)
/Bucks/FB2: C13.2, R12.2, R13.1, U2.5 (FB)
/Bucks/INJ1: C5.1, C6.1, R8.2
/Bucks/INJ2: C12.1, C13.1, R14.2
/Bucks/LED12_A: D2.2 (A), R17.2
/Bucks/LED33_A: D3.2 (A), R18.2
/Bucks/RON1: R5.1, U1.4 (RON)
/Bucks/RON2: R11.1, U2.4 (RON)
/Bucks/SW1: C4.2, L1.1, R8.1, U1.8 (SW)
/Bucks/SW2: C11.2, L2.1, R14.1, U2.8 (SW)
/Bucks/V12_OUT: F2.2, J4.1, R17.1
GND: C7.2, C8.2, C9.2, C10.2, C14.2, C15.2, C16.2, C17.2, D2.1 (K), D3.1 (K), J4.2, R4.2, R5.2, R7.2, R10.2, R11.2, R13.2, R16.2, U1.1 (GND), U1.9 (EP), U2.1 (GND), U2.9 (EP); also elsewhere on the board
VBUS: C7.1, C8.1, C14.1, C15.1, R3.1, R9.1, U1.2 (VIN), U2.2 (VIN); also elsewhere on the board

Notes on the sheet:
3V3 BUCK U1 LM5164, 200 kHz
12 V AUX BUCK U2 LM5164, 300 kHz

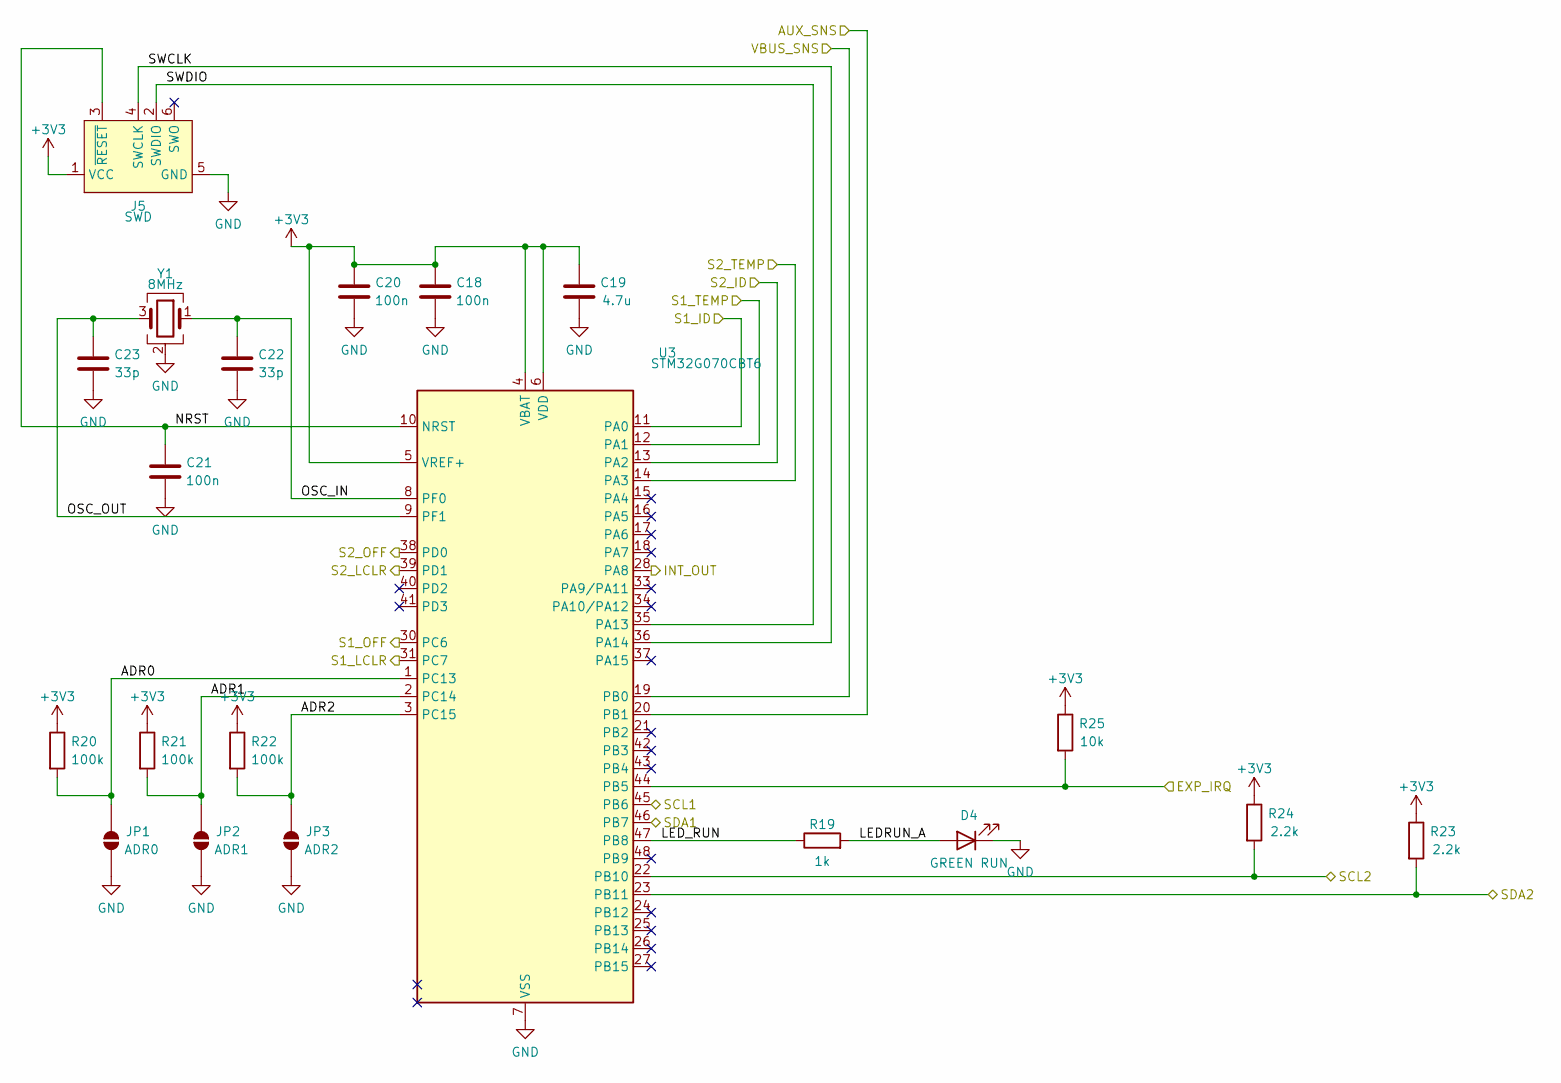
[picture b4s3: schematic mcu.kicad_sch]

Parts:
C18, C20, C21: 100n; C_0402_1005Metric; LCSC C1525
C19: 4.7u; C_0603_1608Metric
C22, C23: 33p; C_0402_1005Metric
D4: GREEN RUN; LED_0603_1608Metric; LCSC C2297
J5: SWD; Tag-Connect_TC2030-IDC-NL_2x03_P1.27mm_Vertical
JP1: ADR0; SolderJumper-2_P1.3mm_Open_RoundedPad1.0x1.5mm
JP2: ADR1; SolderJumper-2_P1.3mm_Open_RoundedPad1.0x1.5mm
JP3: ADR2; SolderJumper-2_P1.3mm_Open_RoundedPad1.0x1.5mm
R19: 1k; R_0402_1005Metric; LCSC C11702
R20, R21, R22: 100k; R_0402_1005Metric; LCSC C25741
R23, R24: 2.2k; R_0402_1005Metric; LCSC C25879
R25: 10k; R_0402_1005Metric; LCSC C25744
U3: STM32G070CBT6; LQFP-48_7x7mm_P0.5mm; LCSC C529338
Y1: 8MHz; Crystal_SMD_3225-4Pin_3.2x2.5mm; LCSC C7424755

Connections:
+3V3: C18.1, C19.1, C20.1, J5.1 (VCC), R20.1, R21.1, R22.1, R23.1, R24.1, R25.1, U3.4 (VBAT), U3.5 (VREF+), U3.6 (VDD); also elsewhere on the board
/AUX_SNS: U3.20 (PB1); also elsewhere on the board
/EXP_IRQ: R25.2, U3.44 (PB5); also elsewhere on the board
/INT_OUT: U3.28 (PA8); also elsewhere on the board
/MCU/ADR0: JP1.1 (A), R20.2, U3.1 (PC13)
/MCU/ADR1: JP2.1 (A), R21.2, U3.2 (PC14)
/MCU/ADR2: JP3.1 (A), R22.2, U3.3 (PC15)
/MCU/LEDRUN_A: D4.2 (A), R19.2
/MCU/LED_RUN: R19.1, U3.47 (PB8)
/MCU/NRST: C21.1, J5.3 (~RESET), U3.10 (NRST)
/MCU/OSC_IN: C22.1, U3.8 (PF0), Y1.1
/MCU/OSC_OUT: C23.1, U3.9 (PF1), Y1.3
/MCU/SWCLK: J5.4 (SWCLK), U3.36 (PA14)
/MCU/SWDIO: J5.2 (SWDIO), U3.35 (PA13)
/S1_ID: U3.11 (PA0); also elsewhere on the board
/S1_LCLR: U3.31 (PC7); also elsewhere on the board
/S1_OFF: U3.30 (PC6); also elsewhere on the board
/S1_TEMP: U3.12 (PA1); also elsewhere on the board
/S2_ID: U3.13 (PA2); also elsewhere on the board
/S2_LCLR: U3.39 (PD1); also elsewhere on the board
/S2_OFF: U3.38 (PD0); also elsewhere on the board
/S2_TEMP: U3.14 (PA3); also elsewhere on the board
/SCL1: U3.45 (PB6); also elsewhere on the board
/SCL2: R24.2, U3.22 (PB10); also elsewhere on the board
/SDA1: U3.46 (PB7); also elsewhere on the board
/SDA2: R23.2, U3.23 (PB11); also elsewhere on the board
/VBUS_SNS: U3.19 (PB0); also elsewhere on the board
GND: C18.2, C19.2, C20.2, C21.2, C22.2, C23.2, D4.1 (K), J5.5 (GND), JP1.2 (B), JP2.2 (B), JP3.2 (B), U3.7 (VSS), Y1.2 (G), Y1.4 (G); also elsewhere on the board
